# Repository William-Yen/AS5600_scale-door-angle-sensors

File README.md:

# AS5600_scale-door-angle-sensors
 Door angle sensor boards and I2C multiplexer board. Created for use in the 1/20th scale "IoT Sandbox" of the New Futures project squad at Industrial Design at TU/e.

 This repository contains the .step files, and KiCAD PCB design files, and Arduino code for replicating the project. Each multiplexer board allows interfacing with up to 24 sensors, and up to 2 multiplexer boards can be used on one I2C bus. 

 ### Note- Silkscreen Mistake
 The A0 and A2 headers corresponding to both U2 and U3 of the multiplexer boards are switched, meaning that the silkscreen markings are wrong. Keep this in mind when setting I2C addresses for U2 and U3.

 ## Electronics Hardware and Assembly
 Two types of custom basic 2-layer PCBs will need to be manufactured. Populating them requires generic breakout boards for the AS5600 magnetic encoder and TCA9548A I2C multiplexer. As donor boards, these are used for the passive components and ICs, as well as the included diametric magnet and headers included with the encoder. 
 
 M2 screws, header jumpers, JST-PH female and male connectors will need to be separately sourced, with the amount depending on how many sensors are used. The reset button on the multiplexer board is optional. The following is a list of hardware used for the final setup; total hardware cost was around 100 Euro for 24 sensors and 1 multiplexer board (populated), with several spare, unpopulated PCBs.

|     Hardware                | Quantity |  Link                                                                                                                                                       |  Notes  |
|:---------------------------:|:--------:|:-----------------------------------------------------------------------------------------------------------------------------------------------------------:|:--------|
|  Sensor board PCBs          |  24      |                                   NA                                                                    |  custom fabricated PCB                                      |
|  Multiplexer board PCBs     |  1       |                                   NA                                                                    |  custom fabricated PCB                                      |
|  AS5600 donor boards        |  24      |  [Aliexpress](https://www.aliexpress.com/item/1005006246654932.html)                                    |  white breakout PCBs, with headers and diametric magnet     |
|  TCA9548A donor boards      |  3       |  [Aliexpress](https://www.aliexpress.com/item/1005006263235377.html)                                    |  purple breakout PCBs, with headers                         |
|  JST-PH male, 5-pin         |  48      |  [LCSC](https://www.lcsc.com/product-detail/Wire-To-Board-Wire-To-Wire-Connector_JST-B5B-PH-K-S-LF-SN_C157993.html)                                         |         |
|  JST-PH female, 5-pin       |  48      |  [LCSC](https://www.lcsc.com/product-detail/Rectangular-Connectors-Housings_JST-PHR-5_C157953.html)                                                         |         |
|  JST-PH female, 4-pin       |  1       |  [LCSC](https://www.lcsc.com/product-detail/Wire-To-Board-Wire-To-Wire-Connector_span-style-background-color-ff0-JST-span-B4B-PH-K-S-LF-SN_C131334.html)    |         |
|  JST-PH female terminal     |  48      |  [LCSC](https://www.lcsc.com/product-detail/Line-Pressing-Terminals_JST-SPA-001T-P0-5_C264002.html)                                                         |         |
|  2.54mm header jumpers      |  26      |  [LCSC](https://www.lcsc.com/product-detail/Shunts-Jumpers_HanElectricity-HY-2540-A0NIB_C18185737.html) | 1 for each sensor and 2 for setting multiplexer addresses   |
|  6.00mm x 3.60mm SMD switch |  1       |  [LCSC](https://www.lcsc.com/product-detail/Tactile-Switches_HYP-Hongyuan-Precision-1TS002C-2400-4300-CT_C319341.html)                                      |         |
|  Assorted wires             |  N/A     |                                   NA                                                                    |  wires to crimp and connect sensors to multiplexer board    |
|  M2x5mm Philips-head screws |  48      |                                   NA                                                                    |  screws to attach sensor boards to the door frame mount     |
|  M2x10mm hex screws         |  24      |                                   NA                                                                    |  screw to attach the door and hinge to the door frame       |
### Assembling the Angle Sensor Boards
Soldering the JST-PH connector to the board first is recommended. Either a horizontal connector can be used (with pins trimmed post-soldering), or vertical connectors with the pins bent 90 degrees. A hotplate or hot air gun from below the PCB is recommmended due to the low melting temperatures of the plastic connector housing.

All SMD components from the generic AS5600 breakout boards can be transferred via hot air or hand soldering; component numbering is the same on the donor boards and custom PCB. Footprints were chosen for 0402 size resistors and capacitors, but 0603 (as was noticed on some purchased boards) will also fit; ensure R2, R3, and R4 are not bridged if passives are 0603. The headers can also be soldered after.

A jumper is required to select either clockwise or counter-clockwise as the positive direction for the rotational values. The programming pin for burning rotation range is also broken out via a header, but it is not used nor necessary for this project.

### Assembling the I2C Multiplexer Board
All resistors used in the TCA9548A breakout boards are the same; therefore only capacitor positions have been marked on the silkscreen. It is recommended to solder the SMD components before the through-hole connectors and headers. Jumpers 

## 3D Printing and Mounting
_____.step, _____.step, and _____.step are the doorframe, door, and door hinge files respectively. One M2x__mm hex screw is used for assembly. This is the original main door structure in the IoT Sandbox, designed by Joep Frens. _____.step is the adapter from M2x10mm hex screw to the magnet, and _____.step is the sensor mount which press fits into frame. Two M2x5mm philips screws secure the sensor board to the mount.

3 M4 screws can be used to secure the multiplexer board if desired.

## Software
_____.ino is the program that runs on an ESP32 Dev Module and interfaces via I2C to the multiplexer board. The code requires the following libraries:

https://github.com/RobTillaart/TCA9548

https://github.com/RobTillaart/AS5600

The ESP32 uses the default I2C pins to connect to the multiplexer board, with SDA on GPIO21 and SCL on GPIO22. The addresses of the multiplexer ICs are set via the jumpers to U1: 0x70; U2: 0x71, and U3, 0x72.

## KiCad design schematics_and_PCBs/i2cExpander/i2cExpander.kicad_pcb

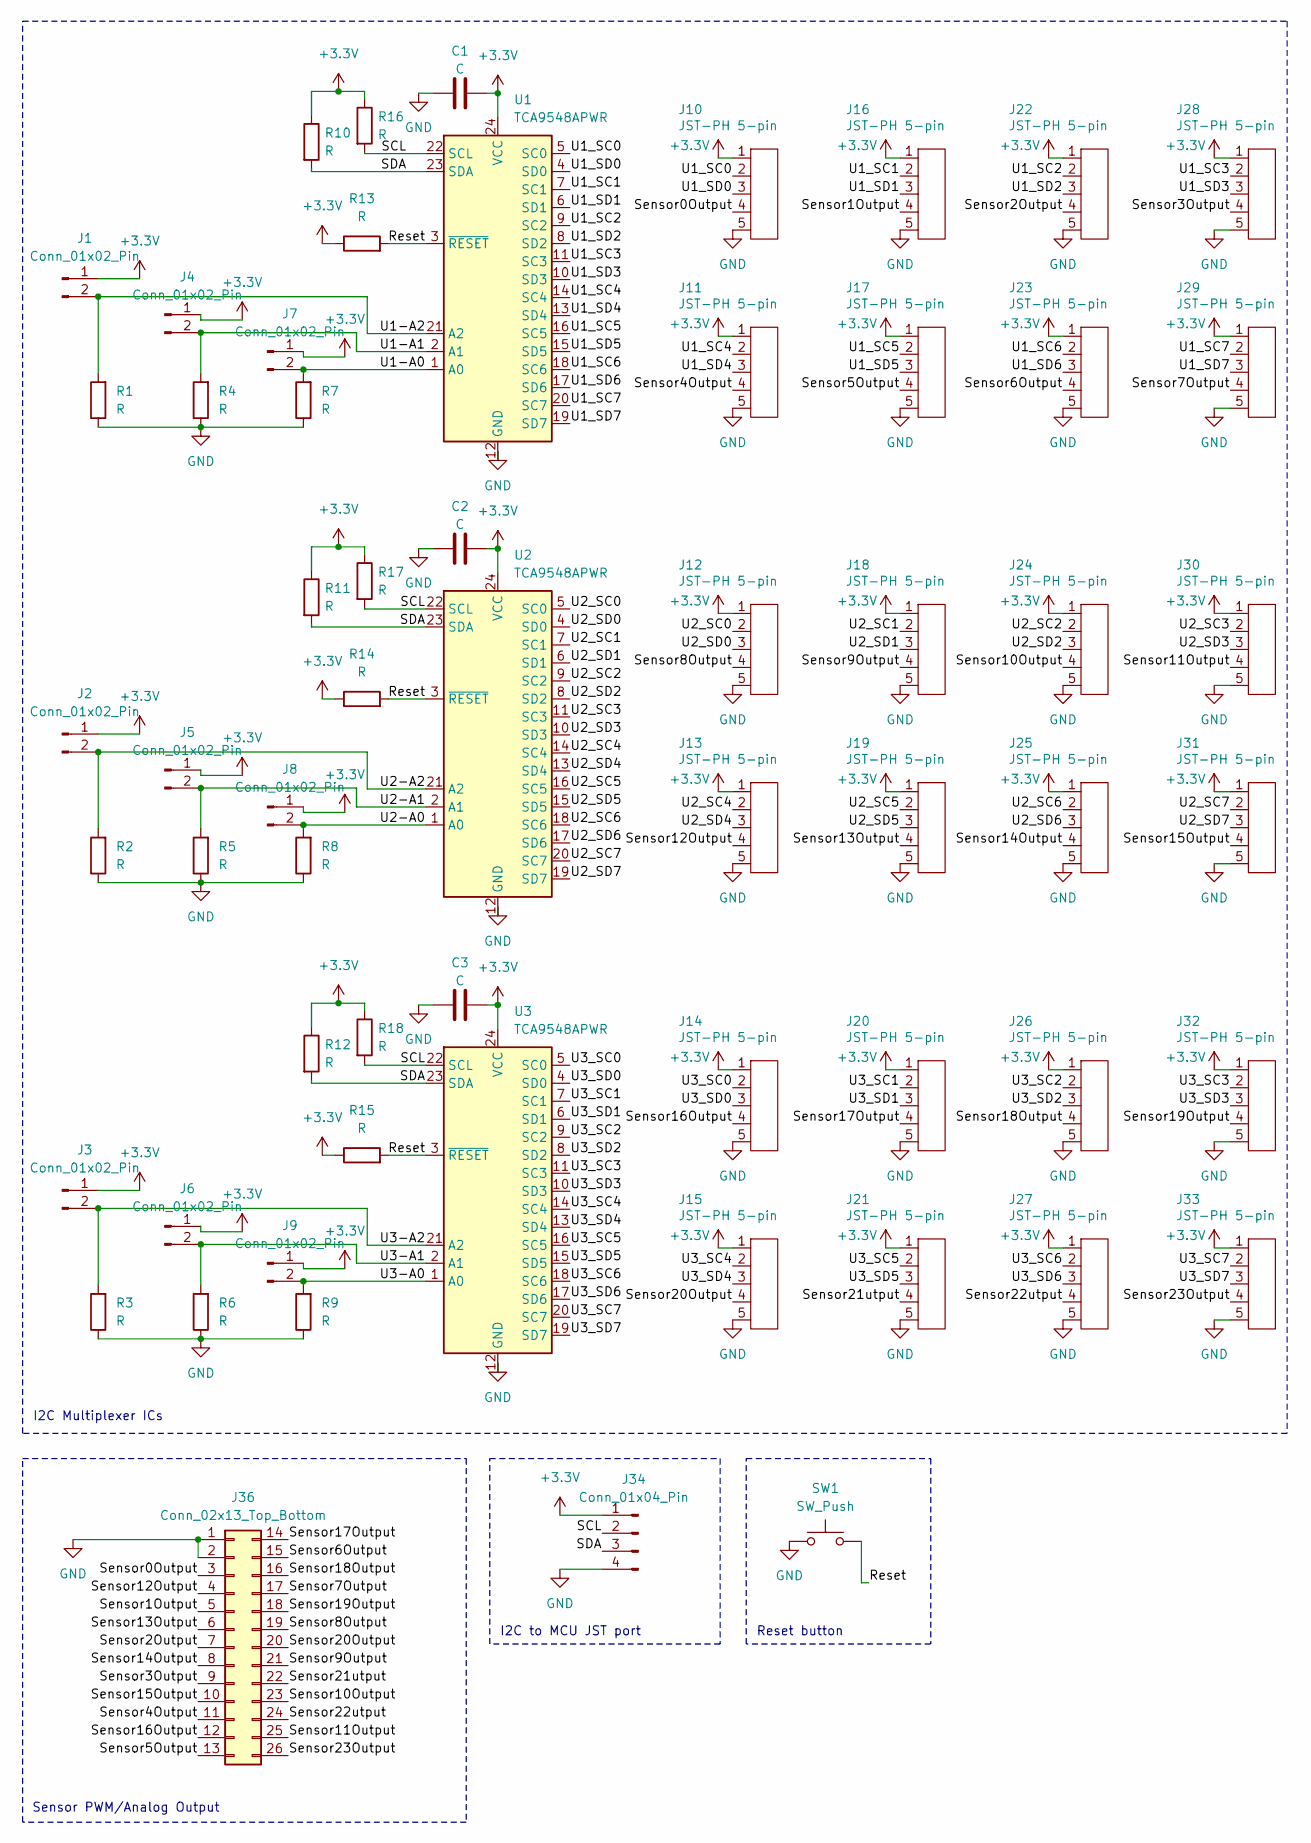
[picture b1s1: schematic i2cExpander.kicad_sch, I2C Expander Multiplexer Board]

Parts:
C1, C2, C3: C; C_0805_2012Metric_Pad1.18x1.45mm_HandSolder
J1, J2, J3, J4, J5, J6, J7, J8, J9: Conn_01x02_Pin; PinHeader_1x02_P2.54mm_Vertical
J10, J11, J12, J13, J14, J15, J16, J17, J18, J19, J20, J21, J22, J23, J24, J25, J26, J27, J28, J29, J30, J31, J32, J33: JST-PH 5-pin; JST_PH_B5B-PH-K_1x05_P2.00mm_Vertical
J34: Conn_01x04_Pin; JST_PH_B4B-PH-K_1x04_P2.00mm_Vertical
J36: Conn_02x13_Top_Bottom; PinHeader_2x13_P2.54mm_Vertical
R1, R2, R3, R4, R5, R6, R7, R8, R9, R10, R11, R12, R13, R14, R15, R16, R17, R18: R; R_0805_2012Metric_Pad1.20x1.40mm_HandSolder
SW1: SW_Push; SW_SPST_CK_RS282G05A3
U1, U2, U3: TCA9548APWR; SOP65P640X120-24N

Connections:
+3.3V: C1.2, C2.2, C3.2, J1.1, J2.1, J3.1, J4.1, J5.1, J6.1, J7.1, J8.1, J9.1, J10.1, J11.1, J12.1, J13.1, J14.1, J15.1, J16.1, J17.1, J18.1, J19.1, J20.1, J21.1, J22.1, J23.1, J24.1, J25.1, J26.1, J27.1, J28.1, J29.1, J30.1, J31.1, J32.1, J33.1, J34.1, R10.1, R11.1, R12.1, R13.1, R14.1, R15.1, R16.1, R17.1, R18.1, U1.24 (VCC), U2.24 (VCC), U3.24 (VCC)
/Reset: R13.2, R14.2, R15.2, SW1.2, U1.3 (~RESET), U2.3 (~RESET), U3.3 (~RESET)
/SCL: J34.2, R16.2, R17.2, R18.2, U1.22 (SCL), U2.22 (SCL), U3.22 (SCL)
/SDA: J34.3, R10.2, R11.2, R12.2, U1.23 (SDA), U2.23 (SDA), U3.23 (SDA)
/Sensor0Output: J10.4, J36.3
/Sensor1Output: J16.4, J36.5
/Sensor2Output: J22.4, J36.7
/Sensor3Output: J28.4, J36.9
/Sensor4Output: J11.4, J36.11
/Sensor5Output: J17.4, J36.13
/Sensor6Output: J23.4, J36.15
/Sensor7Output: J29.4, J36.17
/Sensor8Output: J12.4, J36.19
/Sensor9Output: J18.4, J36.21
/Sensor10Output: J24.4, J36.23
/Sensor11Output: J30.4, J36.25
/Sensor12Output: J13.4, J36.4
/Sensor13Output: J19.4, J36.6
/Sensor14Output: J25.4, J36.8
/Sensor15Output: J31.4, J36.10
/Sensor16Output: J14.4, J36.12
/Sensor17Output: J20.4, J36.14
/Sensor18Output: J26.4, J36.16
/Sensor19Output: J32.4, J36.18
/Sensor20Output: J15.4, J36.20
/Sensor21utput: J21.4, J36.22
/Sensor22utput: J27.4, J36.24
/Sensor23Output: J33.4, J36.26
/U1-A0: J7.2, R7.2, U1.1 (A0)
/U1-A1: J4.2, R4.2, U1.2 (A1)
/U1-A2: J1.2, R1.2, U1.21 (A2)
/U1_SC0: J10.2, U1.5 (SC0)
/U1_SC1: J16.2, U1.7 (SC1)
/U1_SC2: J22.2, U1.9 (SC2)
/U1_SC3: J28.2, U1.11 (SC3)
/U1_SC4: J11.2, U1.14 (SC4)
/U1_SC5: J17.2, U1.16 (SC5)
/U1_SC6: J23.2, U1.18 (SC6)
/U1_SC7: J29.2, U1.20 (SC7)
/U1_SD0: J10.3, U1.4 (SD0)
/U1_SD1: J16.3, U1.6 (SD1)
/U1_SD2: J22.3, U1.8 (SD2)
/U1_SD3: J28.3, U1.10 (SD3)
/U1_SD4: J11.3, U1.13 (SD4)
/U1_SD5: J17.3, U1.15 (SD5)
/U1_SD6: J23.3, U1.17 (SD6)
/U1_SD7: J29.3, U1.19 (SD7)
/U2-A0: J8.2, R8.2, U2.1 (A0)
/U2-A1: J5.2, R5.2, U2.2 (A1)
/U2-A2: J2.2, R2.2, U2.21 (A2)
/U2_SC0: J12.2, U2.5 (SC0)
/U2_SC1: J18.2, U2.7 (SC1)
/U2_SC2: J24.2, U2.9 (SC2)
/U2_SC3: J30.2, U2.11 (SC3)
/U2_SC4: J13.2, U2.14 (SC4)
/U2_SC5: J19.2, U2.16 (SC5)
/U2_SC6: J25.2, U2.18 (SC6)
/U2_SC7: J31.2, U2.20 (SC7)
/U2_SD0: J12.3, U2.4 (SD0)
/U2_SD1: J18.3, U2.6 (SD1)
/U2_SD2: J24.3, U2.8 (SD2)
/U2_SD3: J30.3, U2.10 (SD3)
/U2_SD4: J13.3, U2.13 (SD4)
/U2_SD5: J19.3, U2.15 (SD5)
/U2_SD6: J25.3, U2.17 (SD6)
/U2_SD7: J31.3, U2.19 (SD7)
/U3-A0: J9.2, R9.2, U3.1 (A0)
/U3-A1: J6.2, R6.2, U3.2 (A1)
/U3-A2: J3.2, R3.2, U3.21 (A2)
/U3_SC0: J14.2, U3.5 (SC0)
/U3_SC1: J20.2, U3.7 (SC1)
/U3_SC2: J26.2, U3.9 (SC2)
/U3_SC3: J32.2, U3.11 (SC3)
/U3_SC4: J15.2, U3.14 (SC4)
/U3_SC5: J21.2, U3.16 (SC5)
/U3_SC6: J27.2, U3.18 (SC6)
/U3_SC7: J33.2, U3.20 (SC7)
/U3_SD0: J14.3, U3.4 (SD0)
/U3_SD1: J20.3, U3.6 (SD1)
/U3_SD2: J26.3, U3.8 (SD2)
/U3_SD3: J32.3, U3.10 (SD3)
/U3_SD4: J15.3, U3.13 (SD4)
/U3_SD5: J21.3, U3.15 (SD5)
/U3_SD6: J27.3, U3.17 (SD6)
/U3_SD7: J33.3, U3.19 (SD7)
GND: C1.1, C2.1, C3.1, J10.5, J11.5, J12.5, J13.5, J14.5, J15.5, J16.5, J17.5, J18.5, J19.5, J20.5, J21.5, J22.5, J23.5, J24.5, J25.5, J26.5, J27.5, J28.5, J29.5, J30.5, J31.5, J32.5, J33.5, J34.4, J36.1, J36.2, R1.1, R2.1, R3.1, R4.1, R5.1, R6.1, R7.1, R8.1, R9.1, SW1.1, U1.12 (GND), U2.12 (GND), U3.12 (GND)

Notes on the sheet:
I2C Multiplexer ICs
I2C to MCU JST port
Sensor PWM/Analog Output
Reset button

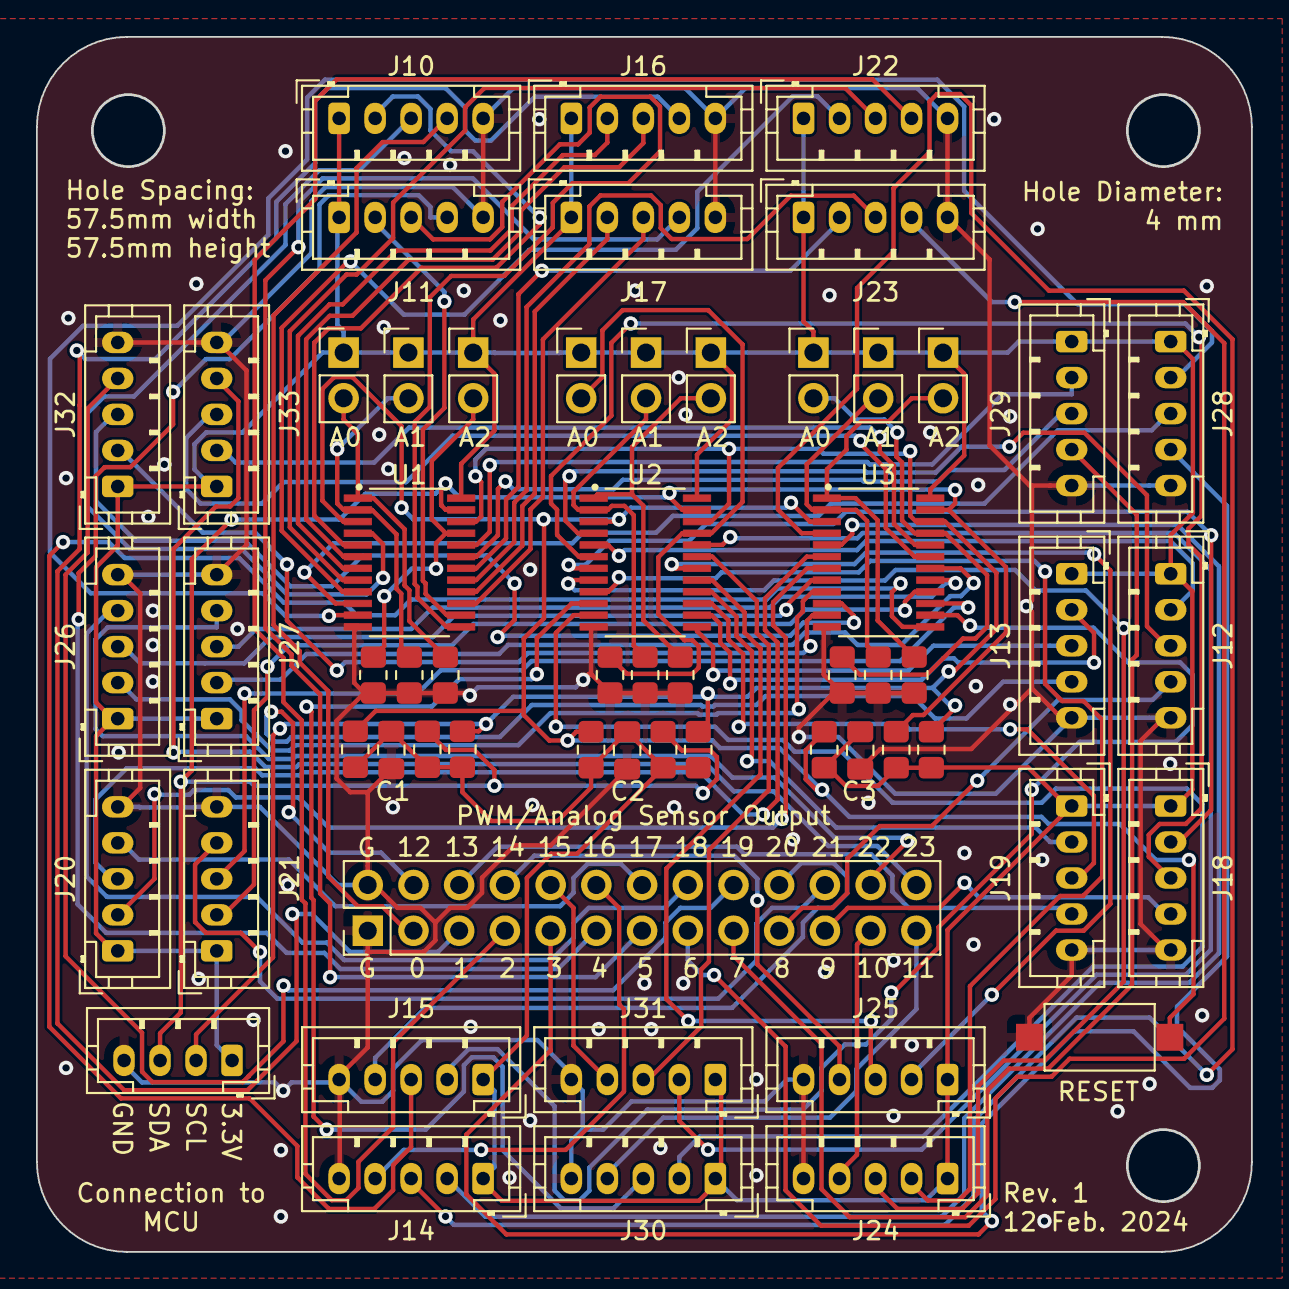
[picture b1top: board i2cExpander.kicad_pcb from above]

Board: 2 copper layers, 67.5 x 67.5 mm, 60 parts (0 on the bottom side), 86 nets.

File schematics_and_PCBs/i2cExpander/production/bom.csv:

Designator,Footprint,Quantity,Value,LCSC Part #
"C1, C2, C3",0805,3,C,
"J1, J2, J3, J4, J5, J6, J7, J8, J9",PinHeader_1x02_P2.54mm_Vertical,9,Conn_01x02_Pin,
"J10, J11, J12, J13, J14, J15, J16, J17, J18, J19, J20, J21, J22, J23, J24, J25, J26, J27, J28, J29, J30, J31, J32, J33",JST_PH_B5B-PH-K_1x05_P2.00mm_Vertical,24,JST-PH 5-pin,
J34,JST_PH_B4B-PH-K_1x04_P2.00mm_Vertical,1,Conn_01x04_Pin,
J36,PinHeader_2x13_P2.54mm_Vertical,1,Conn_02x13_Top_Bottom,
"R1, R10, R11, R12, R13, R14, R15, R16, R17, R18, R2, R3, R4, R5, R6, R7, R8, R9",0805,18,R,
SW1,SW_SPST_CK_RS282G05A3,1,SW_Push,
"U1, U2, U3",SOP65P640X120-24N,3,TCA9548APWR,

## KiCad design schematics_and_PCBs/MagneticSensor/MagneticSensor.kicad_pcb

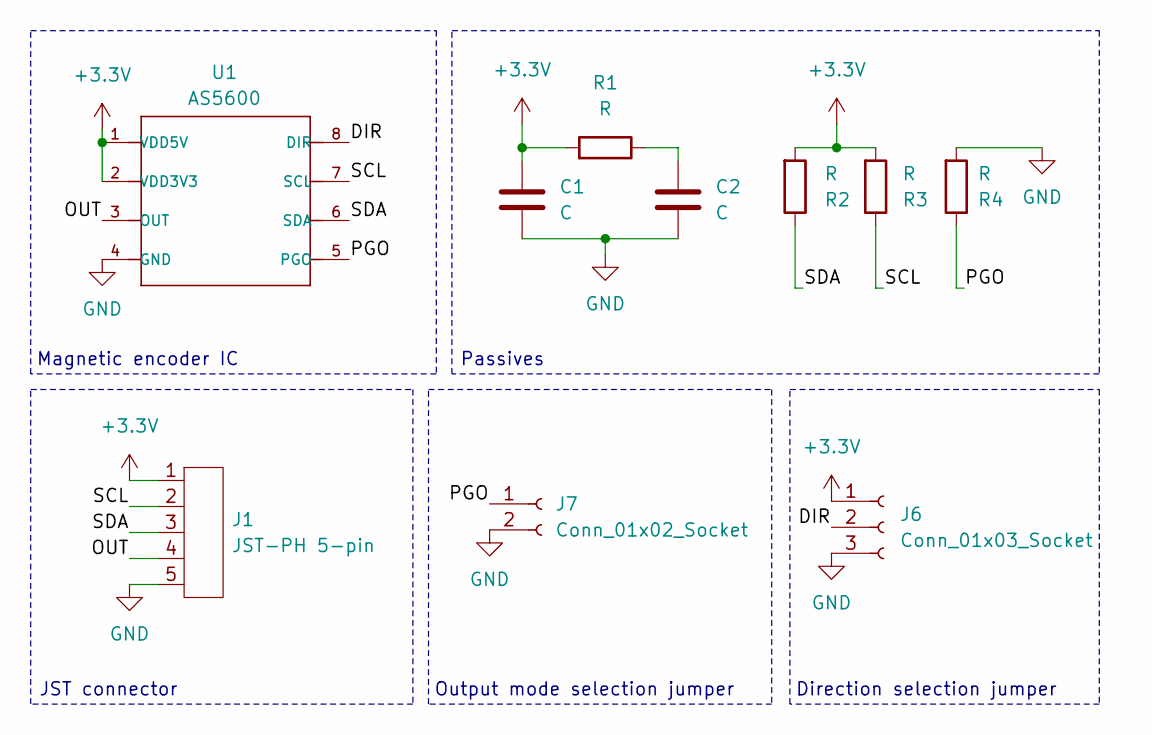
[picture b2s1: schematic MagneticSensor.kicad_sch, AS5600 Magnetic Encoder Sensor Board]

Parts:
C1, C2: C; C_0603_1608Metric
J1: JST-PH 5-pin; JST_5pin_SMD_vertical_foldedpins
J6: Conn_01x03_Socket; PinHeader_1x03_P2.54mm_Vertical
J7: Conn_01x02_Socket; PinHeader_1x02_P2.54mm_Vertical
R1, R2, R3, R4: R; R_0603_1608Metric
U1: AS5600

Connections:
+3.3V: C1.1, J1.1, J6.1, R1.2, R2.2, R3.2, U1.1 (VDD5V), U1.2 (VDD3V3)
/DIR: J6.2, U1.8 (DIR)
/OUT: J1.4, U1.3 (OUT)
/PGO: J7.1, R4.1, U1.5 (PGO)
/SCL: J1.2, R3.1, U1.7 (SCL)
/SDA: J1.3, R2.1, U1.6 (SDA)
GND: C1.2, C2.2, J1.5, J6.3, J7.2, R4.2, U1.4 (GND)
unnamed: C2.1, R1.1

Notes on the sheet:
Magnetic encoder IC
Direction selection jumper
JST connector
Passives
Output mode selection jumper

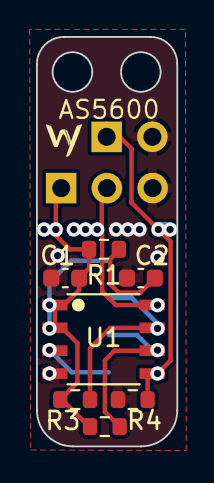
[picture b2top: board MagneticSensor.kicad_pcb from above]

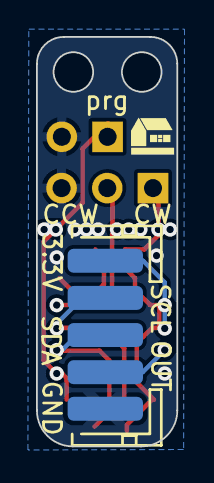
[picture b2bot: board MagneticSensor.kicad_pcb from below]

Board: 2 copper layers, 7.8 x 22.8 mm, 10 parts (3 on the bottom side), 8 nets.

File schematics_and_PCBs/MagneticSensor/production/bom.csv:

Designator,Footprint,Quantity,Value,LCSC Part #
"C1, C2",0603,2,C,
J1,JST_5pin_SMD_vertical_foldedpins,1,JST-PH 5-pin,
J6,PinHeader_1x03_P2.54mm_Vertical,1,Conn_01x03_Socket,
J7,PinHeader_1x02_P2.54mm_Vertical,1,Conn_01x02_Socket,
"R1, R2, R3, R4",0603,4,R,
U1,AS5600,1,AS5600,

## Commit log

2024-03-03 First README.md writeup
    Work still required
    - Add pictures to readme
    - Need to check permissions for uploading door files to this repository
    - Migrate all KiCAD, .step, and Arduino files to repository
    - Finalize Arduino code
2024-03-03 Add pictures, EDA files, directories for 3d files and code
